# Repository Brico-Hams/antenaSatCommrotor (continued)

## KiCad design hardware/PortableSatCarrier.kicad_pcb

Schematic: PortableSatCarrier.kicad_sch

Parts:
C1: 220u_35V_LOW_ESR; C1_capacitor
C2: 220u_35V_LOW_ESR; C2_capacitor
C3: 100n_50V; C3_capacitor
C4: 100n_50V; C4_capacitor
C5: 100n_50V; C5_capacitor
D1: SB560_REVERSE_BLOCK; D1_diode
D2: SMBJ15A_TVS; D2_tvs
F1: T3.15A_MAIN; F1_fuse
F2: T2.5A_MOTOR; F2_fuse
F3: T1A_LOGIC_5V; F3_fuse
F4: T1A_BUCK_INPUT; F4_fuse
J1: DC_IN_12V; J1_terminal
J2: LATCHED_STOP_POWER_OUT_RETURN; J2_terminal
J3: STOP_N_NC_AUX_ONLY; J3_xh
J4: EXTERNAL_BUCK_INPUT; J4_terminal
J5: EXTERNAL_BUCK_5V_RETURN; J5_terminal
J6: GNSS_3V3_UART; J6_xh
J7: AZ_AS5600_I2C0; J7_xh
J8: EL_AS5600_I2C1; J8_xh
J9: OPTIONAL_IMU_MAG_I2C0; J9_xh
J10: AZ_MIN_N_NC_AUX_ONLY; J10_xh
J11: AZ_MAX_N_NC_AUX_ONLY; J11_xh
J12: EL_MIN_N_NC_AUX_ONLY; J12_xh
J13: EL_MAX_N_NC_AUX_ONLY; J13_xh
JM1: AZ_MOTOR; JM1_terminal
JM2: EL_MOTOR; JM2_terminal
JP1: REMOVE_FOR_USB; JP1_header
R1: 10k; R1_resistor
R2: 10k; R2_resistor
R3: 10k; R3_resistor
R4: 10k; R4_resistor
R5: 10k; R5_resistor
R6: 10k; R6_resistor
R7: 4k7; R7_resistor
R8: 4k7; R8_resistor
R9: 4k7; R9_resistor
R10: 4k7; R10_resistor
U1: ESP32_DEVKITC_V4_38_WROOM32E; U1_module
U2: WATTEROTT_TMC2209_V2; U2_driver
U3: WATTEROTT_TMC2209_V2; U3_driver

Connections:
3V3: C3.1 (3V3), C4.1 (3V3), C5.1 (3V3), J6.1 (3V3), J7.1 (3V3), J8.1 (3V3), J9.1 (3V3), R1.1 (3V3), R2.1 (3V3), R3.1 (3V3), R4.1 (3V3), R5.1 (3V3), R6.1 (3V3), R7.1 (3V3), R8.1 (3V3), R9.1 (3V3), R10.1 (3V3), U1.1 (3V3), U2.2 (3V3), U2.3 (3V3), U2.15 (3V3), U3.2 (3V3), U3.3 (3V3), U3.15 (3V3)
AZ_DIR: U1.11 (AZ_DIR), U2.8 (AZ_DIR)
AZ_M1A: JM1.3 (AZ_M1A), U2.13 (AZ_M1A)
AZ_M1B: JM1.4 (AZ_M1B), U2.14 (AZ_M1B)
AZ_M2A: JM1.2 (AZ_M2A), U2.12 (AZ_M2A)
AZ_M2B: JM1.1 (AZ_M2B), U2.11 (AZ_M2B)
AZ_MAX_N: J11.1 (AZ_MAX_N), R4.2 (AZ_MAX_N), U1.3 (AZ_MAX_N)
AZ_MIN_N: J10.1 (AZ_MIN_N), R3.2 (AZ_MIN_N), U1.6 (AZ_MIN_N)
AZ_SCL: J7.4 (AZ_SCL), J9.4 (AZ_SCL), R8.2 (AZ_SCL), U1.22 (AZ_SCL)
AZ_SDA: J7.3 (AZ_SDA), J9.3 (AZ_SDA), R7.2 (AZ_SDA), U1.25 (AZ_SDA)
AZ_STEP: U1.10 (AZ_STEP), U2.7 (AZ_STEP)
BUCK5: F3.1 (BUCK5), J5.1 (BUCK5)
BUCK12: F4.2 (BUCK12), J4.1 (BUCK12)
EL_DIR: U1.15 (EL_DIR), U3.8 (EL_DIR)
EL_M1A: JM2.3 (EL_M1A), U3.13 (EL_M1A)
EL_M1B: JM2.4 (EL_M1B), U3.14 (EL_M1B)
EL_M2A: JM2.2 (EL_M2A), U3.12 (EL_M2A)
EL_M2B: JM2.1 (EL_M2B), U3.11 (EL_M2B)
EL_MAX_N: J13.1 (EL_MAX_N), R6.2 (EL_MAX_N), U1.7 (EL_MAX_N)
EL_MIN_N: J12.1 (EL_MIN_N), R5.2 (EL_MIN_N), U1.4 (EL_MIN_N)
EL_SCL: J8.4 (EL_SCL), R10.2 (EL_SCL), U1.27 (EL_SCL)
EL_SDA: J8.3 (EL_SDA), R9.2 (EL_SDA), U1.28 (EL_SDA)
EL_STEP: U1.12 (EL_STEP), U3.7 (EL_STEP)
ENABLE_N: R1.2 (ENABLE_N), U1.9 (ENABLE_N), U2.1 (ENABLE_N), U3.1 (ENABLE_N)
ESP5: JP1.2 (ESP5), U1.19 (ESP5)
FUSED5: F3.2 (FUSED5), JP1.1 (FUSED5)
FUSED12: D2.2 (FUSED12), F1.2 (FUSED12), F2.1 (FUSED12), F4.1 (FUSED12)
GND: C1.2 (GND), C2.2 (GND), C3.2 (GND), C4.2 (GND), C5.2 (GND), D2.1 (GND), J1.2 (GND), J3.2 (GND), J4.2 (GND), J5.2 (GND), J6.2 (GND), J7.2 (GND), J8.2 (GND), J9.2 (GND), J10.2 (GND), J11.2 (GND), J12.2 (GND), J13.2 (GND), U1.14 (GND), U1.20 (GND), U1.26 (GND), U2.4 (GND), U2.10 (GND), U2.16 (GND), U3.4 (GND), U3.10 (GND), U3.16 (GND)
GNSS_RX: J6.4 (GNSS_RX), U1.30 (GNSS_RX)
GNSS_TX: J6.3 (GNSS_TX), U1.31 (GNSS_TX)
PROTECTED12: D1.2 (PROTECTED12), F1.1 (PROTECTED12)
RAW12: D1.1 (RAW12), J1.1 (RAW12)
STOP_N: J3.1 (STOP_N), R2.2 (STOP_N), U1.5 (STOP_N)
STOP_SEND: F2.2 (STOP_SEND), J2.1 (STOP_SEND)
VMOT: C1.1 (VMOT), C2.1 (VMOT), J2.2 (VMOT), U2.9 (VMOT), U3.9 (VMOT)

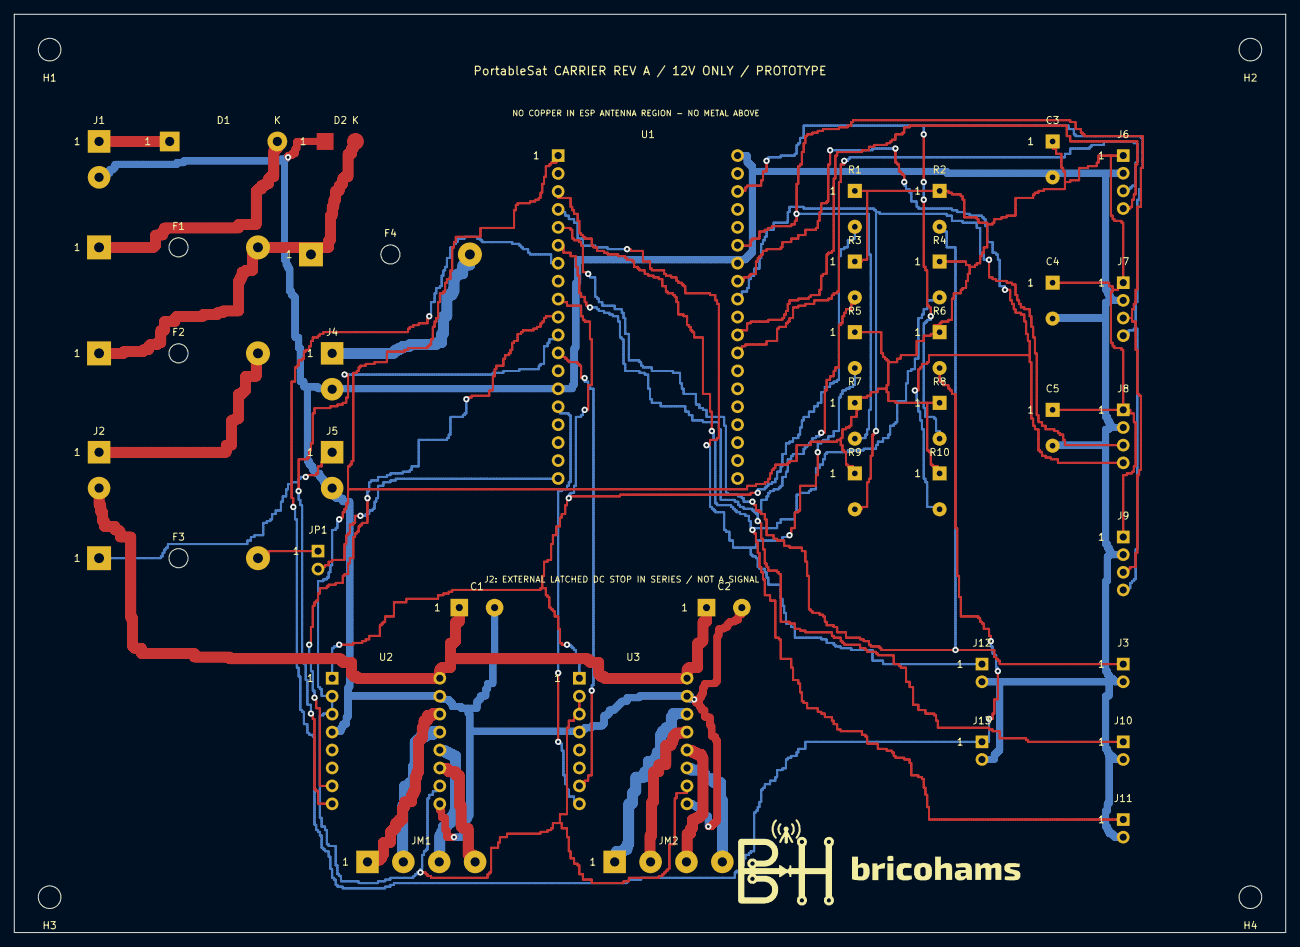
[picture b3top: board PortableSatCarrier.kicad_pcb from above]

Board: 2 copper layers, 180.0 x 130.0 mm, 44 parts (0 on the bottom side), 35 nets.

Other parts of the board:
H1, H2, H3, H4: M3_NPTH; MountingHole_3.2

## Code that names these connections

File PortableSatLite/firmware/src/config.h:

#pragma once
// ---- Pins (ESP32-DevKitC). Change here only. See docs/ELECTRONICS.md for the wiring table. ----
#define PIN_AZ_STEP 26
#define PIN_AZ_DIR  27
#define PIN_EL_STEP 25
#define PIN_EL_DIR  33
#define PIN_EN      14      // TMC2209 EN (active low), shared
#define PIN_AZ_LIM  32      // NC micro-switch to GND, INPUT_PULLUP (open/broken wire = 'pressed' = fail-safe)
#define PIN_EL_LIM  13
#define PIN_GPS_RX  16      // GNSS TX -> ESP32 RX2
#define PIN_GPS_TX  17
#define PIN_SDA0    21      // bus 0: MPU6050 (0x68), QMC5883L (0x0D), AS5600-AZ (0x36)
#define PIN_SCL0    22
#define PIN_SDA1    18      // bus 1: AS5600-EL (0x36)   (two AS5600 share an address -> separate buses)
#define PIN_SCL1    19
// ---- Mechanics ----
#define STEPS_PER_REV   200
#define MICROSTEPS      16
#define GEAR_RATIO      25.0     // 5:1 x 5:1 (cad/gears.py)
#define STEPS_PER_DEG   (STEPS_PER_REV * MICROSTEPS * GEAR_RATIO / 360.0)
#define AZ_MIN_DEG      0.0
#define AZ_MAX_DEG      450.0    // 90 deg of overlap = cable wrap, plus flip
#define EL_MIN_DEG      0.0
#define EL_MAX_DEG      180.0    // 0..180 so the antenna can flip over the zenith
#define MAX_SPEED_DEG_S 20.0
#define ACCEL_DEG_S2    40.0
// ---- Network ----
#define AP_PASS "satlite1234"    // CHANGE before use; minimum 8 characters
